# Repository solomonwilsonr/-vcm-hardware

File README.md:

<h1 align="center">VCM — Version Control for Hardware</h1>

<p align="center">
  Semantic diffs · Evidence-backed impact · Physical fleet traceability
</p>

<p align="center">
  <a href="#quickstart">Get started</a> ·
  <a href="#visual-tour">Visual tour</a> ·
  <a href="docs/architecture.md">Architecture</a> ·
  <a href="docs/hackathon.md">Hackathon</a> ·
  <a href="CONTRIBUTING.md">Contribute</a>
</p>

<p align="center"><strong>Python 3.11+ · Apache-2.0 · Working MVP · Offline core</strong></p>

**Every hardware change has a blast radius. VCM makes it traceable.**

VCM is an engineering-aware version-control and intelligence layer for **datacenter node and rack
hardware**. You commit a node's configuration the way you commit code; VCM tells you what a change
to it breaks, which physical units are affected, and how much to trust each thing it says.

It is built around three questions:

1. **What exactly changed in this configuration?** A semantic diff of the node inventory —
   accelerators, CPUs, memory, NICs, power supplies, slots and the domains they share — not changed
   bytes in a manifest.
2. **What else could that change affect, and what evidence supports it?** A dependency graph plus an
   offline impact report whose findings are labelled `verified`, `rule_based` or `speculative`, each
   with evidence links back to a file and hash.
3. **Which physical units were built from the affected configuration?** Releases pin artifact
   hashes; nodes are registered against releases and can be looked up by component or revision.

> Built for the Appwrite Databases Hackathon: see [docs/hackathon.md](docs/hackathon.md).

> **Status: working MVP, honest scope.** Everything marked *Implemented* below runs and is covered
> by tests in this repository. Everything marked *Planned* does not exist yet. See
> [Limitations](#limitations).

## Explore the documentation

- [Quickstart](#quickstart) — install, compare two revisions and open the dashboard.
- [Hardware workflows](#work-with-your-own-hardware) — inventory, signing, fleet, sync and agents.
- [Appwrite](#what-lives-in-appwrite-and-why) — shared fleet, semantic search and graph storage.
- [Feature status](#modules-implemented-vs-planned) · [Confidence classes](#confidence-classes) · [Limitations](#limitations).
- [Architecture](docs/architecture.md) · [Data model](docs/data-model.md) · [Roadmap](docs/roadmap.md) · [Demo script](docs/demo-script.md).

## The demo in one paragraph

A node runs eight A100 PCIe accelerators on four 2000 W supplies in a 2+2 redundant bank. Someone
proposes swapping them for H100 NVL. The manifest diff is eight replaced line items. What VCM says
is that the node now draws **4190 W against a 4000 W usable budget**, so losing one supply drops it;
that the **installed driver (470.223.02) is below the H100's minimum (525.60.13)**, so the cards
will not initialise at all, and that CUDA 11.4 is below their 12.0 minimum; that the chassis is
rated for 3600 W of cooling; that the Gen5 cards sit on a Gen4 host root; that both PCIe roots are
lane-oversubscribed; and that the power connector changed from 8-pin EPS to 12VHPWR, so the existing
harness does not fit.

None of that is written down anywhere. It falls out of the graph plus a component catalog.

```
$ vcm impact v1.0 v1.1
Findings: verified 6, rule_based 9, speculative 3 | severity: critical 3, warning 9, info 6
```

Then it checks the premise. Fed the machine's own Redfish and `nvidia-smi` output, `vcm drift`
reports that v1.0 was never quite true: a DIMM has failed and the driver actually installed is
older than the one declared. The fleet commands say which racks go over budget if every unit on the
old release is upgraded, and plan the rollout in waves of at most one unit per rack, holding back
every unit whose change still has critical findings.

## Visual tour

An 18-second, silent preview made from existing page captures with camera movement.
The comparison screen is the running dashboard; graph and fleet scenes are landing-page
illustrations. This is an edited tour, not a recording of live telemetry.

### Compare revisions and inspect the evidence

The dashboard brings the revision pair, changed components, impact severity, catalog trust and
confidence classes into one view. This captured demo includes attached machine observations;
its finding counts differ from the declaration-only CLI example above.

<details>
<summary><strong>See the landing page</strong></summary>

The landing page introduces the product. It is deployed at
<http://vcm-site-061664787595.s3-website-us-east-1.amazonaws.com> (S3 static hosting; HTTPS via
CloudFront is pending AWS account verification). Run it locally with
`python3 -m http.server 8080 --directory site`, then open <http://127.0.0.1:8080>.
The authenticated dashboard is served by `vcm serve` below.

</details>

See [media sources and regeneration instructions](docs/assets/README.md).

## Quickstart

### 1. Clone and install

Requires **Python 3.11+**. These commands use a macOS/Linux shell; the demo scripts also
require Bash, Make and `sha256sum` (GNU coreutils). The core has no third-party dependencies;
`.[dev]` installs the API, Appwrite SDK and development tools.

```bash
git clone https://github.com/solomonwilsonr/-vcm-hardware.git
cd -- -vcm-hardware
python3 -m venv .venv
source .venv/bin/activate
python -m pip install -e ".[dev]"
vcm --help
```

### 2. Create a sample hardware repository

Run these from the project root. Keep the sample fleet local even if you already have
Appwrite credentials configured. Choose an empty directory for `my-node`.

```bash
export VCM_FLEET_LOCAL=1
mkdir my-node
cp -R examples/gpu-node/v1.0/. my-node/
vcm init my-node
vcm -C my-node commit -m "Baseline: A100 node" --tag v1.0
cp -R examples/gpu-node/v1.1/. my-node/
vcm -C my-node commit -m "Proposed upgrade: H100 NVL" --tag v1.1
vcm -C my-node diff v1.0 v1.1
vcm -C my-node impact v1.0 v1.1
```

Expect eight accelerator replacements and findings about power, cooling, firmware and
connectors. Each finding carries its confidence class and evidence.

### 3. Open the dashboard

```bash
vcm -C my-node token create demo --role approver
vcm -C my-node serve --port 8000
```

Save the token printed by the first command; it is shown only once. Open
<http://127.0.0.1:8000/#/compare> and paste it into the browser's token prompt.
Select **v1.0** as the base and **v1.1** as the head, then click **Compare**.
Stop the server with `Ctrl+C`.

### 4. Run the complete demo and checks

From the project root, with the virtual environment active:

```bash
make test
make lint
make demo
```

`make demo` adds observed drift, releases, signed unit passports, racks, rollout planning,
reviews and audit verification. It **recreates `demo-workspace/` on each run** and ends by
intentionally corrupting a stored blob to prove that release verification detects tampering.
Use the clean `my-node` repository above for interactive exploration.

### 5. Optional: connect a shared Appwrite fleet

The local walkthrough needs no credentials. To connect a shared fleet, copy
[`.env.example`](.env.example) to `.env` if you do not already have one, fill in your
endpoint, project, API key and database ID, then run:

```bash
unset VCM_FLEET_LOCAL
vcm fleet health
vcm fleet provision
```

The required API-key scopes are documented in `.env.example`. Keep credentials in `.env`;
never commit them. See [the Appwrite guide below](#what-lives-in-appwrite-and-why) for
semantic part search and the optional shared graph. `make demo-fleet` demonstrates two
checkouts sharing the registry and **writes demo units to your configured Appwrite project**.

## Work with your own hardware

On your own node:

```bash
vcm init .
vcm commit -m "current config" --tag v1.0     # snapshot every file, categorised by type
# ...edit the node manifest...
vcm commit -m "proposed upgrade" --tag v1.1
vcm diff v1.0 v1.1                            # semantic diff
vcm impact v1.0 v1.1                          # impact report (--json for JSON)
vcm catalog coverage --rev v1.1               # what the catalog can actually reason about
vcm validate --rev v1.1 --compare v1.0
vcm release create R1 --rev v1.1              # pin hashes
vcm release verify R1
vcm device register NODE-0001 --release R1 --batch RACK-12
vcm device affected --component GPU0 --value "NVIDIA A100 PCIe 40GB"
vcm rollback plan v1.0 --from v1.1
vcm timeline ; vcm explain v1.0 v1.1
```

### Check the declaration against the machine

```bash
vcm inventory fetch-redfish https://10.0.0.21 --user ro --out bmc.json   # explicit network call
nvidia-smi --query-gpu=index,name,serial,pci.bus_id,driver_version,power.draw,power.limit,\
pcie.link.gen.max,pcie.link.width.max --format=csv > gpus.csv
vcm drift --rev v1.0 --redfish bmc.json --nvidia-smi gpus.csv --attach
vcm inventory manifest --redfish bmc.json --out draft.node.json        # bootstrap a manifest
```

Before trusting a new capture, ask it what it left out:

```bash
vcm inventory doctor --redfish bmc.json --nvidia-smi gpus.csv
```

The doctor lists Redfish resources that could not be fetched, kinds that were present but not read,
component types the capture cannot vouch for (drift will not judge them), and parts too thinly
described to match. A parser that is quiet about what it skipped makes a gap look like a clean
result; this is how you find out. To share a capture, or add it to the test suite, scrub it first:

```bash
vcm inventory sanitize --redfish bmc.json --nvidia-smi gpus.csv --out tests/captures/<vendor>-<model>
```

That replaces serials, hostnames, addresses, UUIDs and secrets with stable same-shape stand-ins
(identifiers correlate across files, model names, part numbers and firmware versions are left
alone, and the scrubbed capture parses exactly as the original did), seals the folder with
checksums, and drafts an `expect.json`. The folder then becomes a regression test automatically;
see [`tests/captures/README.md`](tests/captures/README.md). The scrubber cannot know what a site
considers sensitive in free text: read the output before you share it.

`vcm drift` compares only the component types a source can see: a capture without NICs is never
read as "NICs missing". With `--attach`, the observation becomes evidence on the revision, and the
next impact report says whether the base was true, sets measured draw beside the declared estimate,
and projects the new configuration's draw (labelled `speculative`).

### Sign, audit, authenticate

```bash
vcm key gen release-eng --trust               # private key in ~/.vcm/keys, public in trustdb.json
vcm release sign R1 --key release-eng
vcm release verify R1 --require-signature
vcm device sign NODE-0001 --key release-eng
vcm audit verify                              # every commit, release, signature, lock: hash-chained
vcm token create alice --role approver        # API tokens are stored hashed, shown once
vcm serve                                     # binds 127.0.0.1; refuses to start without a token
```

### Fleet

```bash
vcm fleet rack define RACK-12 --budget 17000
vcm fleet place NODE-0001 --rack RACK-12 --position 20      # or: vcm fleet netbox --devices devices.json
vcm fleet query --type gpu --firmware "gpu_driver<535"       # --csv for spreadsheets
vcm fleet recall --mpn M393A4K40DB3                           # grouped by rack and release
vcm fleet power --upgrade-to v1.1 --release R1                # exits 1 if a rack goes over budget
vcm fleet rollout --to v1.1 --release R1 --max-per-rack 1     # waves; blocks critical, defers over-budget
```

### Team sync and locks

```bash
vcm remote add origin /mnt/shared/vcm/gpu-node
vcm push ; vcm pull                            # fast-forward only: VCM never merges hardware
vcm lock acquire gpu-node-01.node.json --reason "re-pinning PSUs" --ttl 4
vcm lock release gpu-node-01.node.json
```

Divergent histories are reported with the way out (compare both sides, keep one, re-apply the
other), never merged. Tags and records that differ between clones are listed as conflicts and left
alone. Commits and pushes that touch a file someone else has locked are refused.

### Let an AI agent use VCM (MCP)

`vcm mcp` serves VCM over the Model Context Protocol on stdio. It runs offline, needs no API key,
and opens no sockets. Point any MCP client at it, for example in `.mcp.json`:

```json
{"mcpServers": {"vcm": {"command": "vcm", "args": ["-C", "/path/to/repo", "mcp"],
                        "env": {"VCM_AGENT_NAME": "claude"}}}}
```

The agent gets 23 read-only tools (diff, impact with confidence labels and evidence, drift against
inline captures, a capture doctor, catalog lookup and review priority, a claim checker, fleet query and recall, rack power, rollout plan, policy check,
release and audit verification, passports, rollback) and two prompts (`review_change`,
`fleet_upgrade_plan`). Its server instructions tell it to report each finding's confidence class and
never upgrade it.

It changes nothing itself. The single write tool, `vcm_propose`, records a **pending proposal** for
one of five actions (create a release, open a review, place a unit, define a rack, register a unit).
A person decides:

```bash
vcm proposal list --status pending
vcm proposal show P0001
vcm proposal approve P0001 --by dana     # performs it as dana, after re-checking it still holds
vcm proposal reject P0001 --by dana --reason "not this quarter"
```

An agent cannot approve, and the person must differ from the proposer. Signing, catalog reviews
(they record that a human checked a datasheet), policy overrides, commits, remotes and locks are
**not proposable**: they stay human. Proposals are validated when made and again when approved; a
release that policy would block cannot even be proposed. The audit log records the agent as
proposer and the person as approver. The API exposes the same decision, needing an `approver`
token.

### Keeping agents honest

An agent can misquote a report: cite a finding that does not exist, promote a `rule_based` finding
to `verified`, round 4190 W into 4000 W, or omit the one critical finding that mattered.
`vcm_check_claims` catches that mechanically before the answer goes out. The agent submits what it
is about to say (finding ids, the confidence class and severity it will state, the numbers it will
quote); VCM recomputes the report itself and returns every mismatch plus every critical finding
that went unmentioned. The `review_change` prompt tells the agent to call it and not to answer
until `honest` is true. It cannot catch bad *reasoning* about correct facts.

`vcm eval` grades an agent on five tricky cases: the headline upgrade, a part the catalog has never
heard of, a base that does not match the machine (and a projection that is only a prediction), a
change that touches nothing (do not invent problems), and instructions planted in a commit message
(data, not orders). Grading is mechanical: claims checked as above, no invented figures or finding
ids, never "safe", and case-specific honesty.

```bash
vcm eval run                         # the honest reference answerer: must pass 5/5
vcm eval run --agent sloppy          # flawed on purpose: must fail (CI checks both)
vcm eval run --agent "python my_agent.py"   # yours; see vcm_mcp.evals.external_agent
```

An external agent gets one JSON object on stdin (`question`, `repo`, `a`, `b`, `mcp_command`) and
prints `{"text": ..., "claims": [...]}`. **No live model has been run against these cases yet.**
Until one has, a pass means only that the grader and the reference agree.

### Policies and site rules

```json
{"schema": "vcm-policy/1", "rules": [
  {"id": "no-critical", "forbid_severity": "critical"},
  {"id": "known-parts", "forbid_unknown_parts": true},
  {"id": "power-needs-two", "require_approvals": 2, "when": {"title_matches": "power|supply"}},
  {"id": "signed", "require_signed_release": true, "stages": ["verify"]}]}
```

Commit this as `vcm-policy.json`. `vcm policy v1.0 v1.1` checks a change; `vcm release create`
refuses a violating release unless `--override-policy REASON` is given, and the override is written
into the manifest and the audit log. Site-specific rules are Python plugins (see
[`examples/plugins/site_rules.py`](examples/plugins/site_rules.py)), enabled with
`VCM_RULE_PLUGINS=module:function` or the `vcm.rules` entry-point group.

### Node manifests

A node is described by a `*.node.json` file. Components declare what they are and which domains
they share; everything else you put on a component is carried through and available to rules.

```json
{
  "schema": "vcm-node/1",
  "node": "gpu-node-01",
  "chassis": {"model": "Supermicro SYS-420GP-TNR", "cooling_w": 3600},
  "power": {"domains": {"PSU_BANK": {"redundancy": "2+2", "watts_each": 2000,
                                     "overhead_w": 400}}},
  "firmware": {"gpu_driver": "535.129.03", "cuda": "12.2"},
  "components": [
    {"ref": "GPU0", "type": "gpu", "model": "NVIDIA H100 NVL 94GB",
     "mpn": "900-21010-0000-000", "slot": "PCIE_SLOT1", "form_factor": "FHFL dual-slot",
     "tdp_w": 400, "pcie_gen": 5, "pcie_lanes": 16, "power_connector": "12VHPWR (16-pin)",
     "connections": {"power": "PSU_BANK", "pcie": "CPU0_PCIE_ROOT",
                     "interconnect": "NVLINK_FABRIC"}}
  ]
}
```

A power domain behaves exactly as a supply rail does on a board, which is why the same graph, diff
and impact engine serve both. Domains shared by every component (a PSU bank, or ground on a board)
are deliberately **not** followed when computing blast radius — otherwise every change would report
the whole node as affected.

## What lives in Appwrite, and why

VCM stores two very different kinds of thing, and they belong in different places.

**Derived data belongs on your disk.** The object store, snapshots and the dependency graph can all
be rebuilt from the design files in front of you. Nothing is lost by keeping them local, so the
graph's default backend is SQLite.

**Facts about physical hardware do not.** A unit is a machine that was built and shipped. It is
registered by whoever is standing in front of it and asked about later by someone else entirely —
an operator planning a rollout, a technician scanning the QR sticker on a front panel, an engineer
running a recall after a bad batch of accelerators. Those are different people on different
machines reasoning about the same hardware.

So the **unit and rack registry is the fleet of record, and it lives in Appwrite TablesDB.** The
local JSON files are a cache. This is not a swappable backend; it is the only arrangement in which
the registry is correct. With a per-clone registry, two engineers who clone the repository have two
different fleets, and this —

```bash
vcm device affected --component GPU0 --value "NVIDIA A100 PCIe 40GB"
```

— silently answers about whichever subset of the fleet that laptop happens to know about. A recall
query is the single question VCM must never get half-right.

```bash
cp .env.example .env     # endpoint, project, API key
vcm fleet health         # is the fleet of record reachable, and how big is it?
vcm fleet provision      # create the fleet tables, columns and indexes
vcm device register NODE-0001 --release R1
vcm fleet recall --model "A100"      # every unit, registered from any machine
```

Two behaviours differ on purpose, because the failure modes are not symmetric:

- **Writes fail closed.** If the fleet of record is unreachable, registering a unit raises and
  nothing is written locally either. A unit recorded only on the laptop that registered it is
  exactly the bug this fixes, so a loud failure beats a half-written registration.
- **Reads degrade open.** Reads fall back to the local mirror when the service is unreachable, but
  the store remembers that it did, and every command that reports to a human prints
  `fleet: LOCAL CACHE, possibly stale`. Stale answers are useful offline; silently stale ones are
  not.

One consequence is worth stating plainly: the registry is shared, but design history is not. A
clone can meet a unit built from a revision it has never fetched, and VCM reports that unit by
serial rather than dropping it or failing the query:

```
DEMO-B1   rack -   release R1   GPU0=NVIDIA A100 PCIe 40GB, ... (+4)
1 unit(s), 8 component(s); by rack: (unplaced) 1
  UNRESOLVED DEMO-A1: revision 9d9e3545fd is not in this checkout (fetch it before closing the incident)
fleet: shared (Appwrite TablesDB)
```

An incident cannot be closed on a silently partial fleet, which is the whole reason the registry
moved out of the checkout.

Without credentials, everything above keeps the old on-disk behaviour with no flags, which is how
the test suite runs. `VCM_FLEET_LOCAL=1` forces it. Repository-scoped records — releases, pull
requests, agent proposals — stay in the checkout, because they travel with the files they describe.

### Semantic part search on VectorsDB

The catalog matches by part-number prefix, which answers *what is this part* and nothing else. When
a part goes end of life the question is the other one — *what could I put here instead* — and
"a dual-slot 300 W accelerator I can run on an existing 8-pin harness" names no part at all.

So the catalog is embedded into **Appwrite VectorsDB** and searched by meaning:

```bash
vcm catalog provision                       # vector collection, dimension probed from the model
vcm catalog index                           # embed all 90 parts
vcm catalog similar "dual-slot 300 W accelerator on an 8-pin harness"
vcm catalog replace "NVIDIA A100 PCIe 40GB"
```

A nearest-neighbour hit is a *plausible* candidate, and plausible is not the standard the rest of
VCM reports at. So `replace` runs every candidate back through the deterministic catalog facts —
type, socket, connector, slot width, PCIe generation, driver floor — and labels it:

```
Replacements for NVIDIA A100 PCIe 40GB (gpu):
  CHECK         NVIDIA H100 NVL  (unreviewed)
                needs a 12VHPWR connector, installed part uses 8-pin EPS
                draws 400 W against 250 W
                requires driver 525.60.13 (installed part needs only 450.80.02)
  INCOMPATIBLE  NVIDIA H100 SXM5  (unreviewed)
                different socket (PCIe vs SXM5)
```

Semantic search proposes; the rule data disposes. The same discipline as the rest of the engine:
nothing is reported as more certain than it is.

### The shared dependency graph

The graph has an Appwrite backend too, for teams that want impact analysis queryable fleet-wide
rather than rebuilt per machine. Unlike the registry this one is genuinely optional — the data is
derived, so SQLite loses nothing but shareability.

```bash
vcm graph provision
vcm graph push --rev v1.1
vcm graph query --component GPU0 --rev v1.1 --backend appwrite
```

Row ids are deterministic hashes, so a re-push upserts rather than duplicating; writes are batched
into bulk upserts; and a revision's subgraph is paged into memory once for traversal, or queried
live with `prefetch=False`. The test suite asserts that an Appwrite-backed graph returns
**byte-identical** results to the local SQLite one.

> **What has actually been run.** Every Appwrite path is exercised against a faithful in-process
> fake (`tests/fake_appwrite.py`) under both SDK response shapes, because the suite must pass
> without network. Beyond that: the **fleet store has been run against a live Appwrite project** —
> provisioned, and verified with two separate clones registering units into one fleet, including
> the cross-clone duplicate rejection and the stale-cache path. The **VectorsDB path has not been
> run live**: it needs the `embeddings.write` and `vectors.*` scopes on the API key, and the
> commands say so when they are missing.

## Modules: implemented vs planned

| # | Module | Location | Status |
|---|--------|----------|--------|
| 1 | Content-addressed object store, snapshots, branches, tags, commit/log/checkout/diff, evidence store | `packages/core` | **Implemented** |
| 2 | Hash-chained audit log of every state change | `packages/core` (`vcm_core.audit`) | **Implemented** |
| 3 | Ed25519 signing of releases and unit passports, trust database | `packages/core` (`vcm_core.signing`) | **Implemented** in pure Python (RFC 8032 vectors tested) |
| 4 | Remotes (shared directory), push/fetch/pull, file locks | `packages/core` (`vcm_core.remote`) | **Implemented**, fast-forward only by design. No S3 or Git transport |
| 5 | Input parsers: node manifests (`*.node.json`), KiCad `.kicad_sch`/`.kicad_pcb`, BOM CSV | `packages/file-parsers` | **Implemented**. Node manifests are the primary format; the board parsers are retained from VCM's origin and still work |
| 6 | Observed inventory: Redfish captures, `nvidia-smi` CSV/XML, manifest drafting | `packages/file-parsers` (`vcm_parsers.inventory`) | **Implemented** against saved captures and a synthetic sample. Live Redfish capture exists but has **not been run against a real BMC** here |
| 7 | Semantic diff engine, and drift (manifest vs machine) | `packages/diff-engine` | **Implemented** |
| 8 | Engineering dependency graph | `services/engineering-graph` | **Implemented**, with two interchangeable backends: local SQLite and **Appwrite TablesDB** for a shared fleet-wide store |
| 9 | Impact analysis | `services/ai-engine` | **Implemented** as a deterministic rule engine over a component catalog. Node rules: power budget under redundancy policy, chassis cooling, PCIe generation and lanes, driver/CUDA/BIOS/BMC minimums, power connector, DDR generation, DIMM mixing and channel population, socket fit and mixed CPUs, mixed accelerators on one fabric, NIC vs fabric speed, slot count, and measured draw from attached observations. LLM provider interface exists with a no-op default; no real LLM provider ships |
| 10 | Rule plugins for site-specific checks | `services/ai-engine` (`vcm_ai.plugins`) | **Implemented**. Plugins cannot emit `verified` findings; a crashing plugin becomes a finding |
| 11 | Component catalog | `services/ai-engine` | **Implemented**: 90 parts across layers, user and project overrides, JSON/CSV import, per-field source attribution, review worksheets ranked by what your units use, and a trust figure on every report. **No bundled part is reviewed** |
| 11b | Semantic part search | `services/ai-engine` (`vcm_ai.semantic`) | **Implemented** on **Appwrite VectorsDB**: the catalog is embedded and searched by meaning, then every candidate is checked against catalog facts and labelled `drop_in`/`check`/`incompatible`. Tested offline against a fake embedding and vector service; **not run against a live VectorsDB** |
| 12 | Validation | `services/validation` | **Implemented**: built-in checks plus an optional `kicad-cli` wrapper for the board domain (skipped when absent) |
| 13 | Release manifests, verification, rollback planner | `packages/workflow` | **Implemented** (JSON/YAML manifest, re-hash verification, signatures, policy record) |
| 14 | Policies as code (`vcm-policy.json`) gating checks, reviews, releases and verification | `packages/workflow` (`vcm_workflow.policy`) | **Implemented** |
| 15 | Physical traceability: unit registry, signed passports, QR | `services/traceability` | **Implemented**. The unit registry is **Appwrite TablesDB** when configured, so one fleet is shared by every machine; local JSON is the offline cache. Pure-Python QR encoder |
| 16 | Fleet: racks, placement, queries, recalls, rack power, rollout waves, NetBox import | `services/traceability` (`vcm_trace.fleet`, `vcm_trace.fleet_store`, `vcm_trace.netbox`) | **Implemented**. Racks and placement share the fleet store; writes fail closed, reads fall back to the cache and say so. NetBox import tested against saved API JSON, **not against a live NetBox** |
| 17 | Change review records | `packages/workflow` | **Partial**: diff, impact, validation, comments, approvals, policy-aware readiness, identity via API tokens. No merge action |
| 18 | Time machine (`timeline`, `explain`) | `packages/workflow` | **Implemented** |
| 19 | CLI, REST API, dashboard | `packages/vcm-cli`, `services/api` | **Implemented**. The API requires a token (roles: viewer, editor, approver, admin) and refuses to start without one unless `--insecure`. The dashboard's **Setup** page draws every part of a node, the domains they share, the attached machine capture, and the units and racks, and re-reads the repository every 5 s ("live" means polling the repository, **not** telemetry from machines: machine data appears only where a capture was attached with `vcm drift --attach`) |
| 20 | Agent access: MCP server (stdio, offline) with read-only tools and a propose-then-human-approves write path | `services/mcp-server` (`vcm_mcp`) | **Implemented**. Tested over a real stdio subprocess; **not yet exercised with a live agent client**. The dashboard's **Agents** page lists proposals and lets a signed-in approver approve or reject them (the API refuses agents, the proposer and unauthenticated callers) |
| 21 | Agent honesty: claim checker (`vcm_check_claims`) and evals (`vcm eval`) | `vcm_ai.claims`, `vcm_mcp.evals` | **Implemented**. Evals have been run only against reference answerers (one honest, five deliberately flawed), **never against a live model** |
| 22 | Integrations and apps: KiCad plugin, FreeCAD, Git bridge, web app, desktop app | `integrations/`, `apps/` | **Planned**: README stubs only |

## Confidence classes

Every finding has exactly one `confidence_class`, plus evidence links (`file` with hash, `ref`,
`commit`, `db` with per-field attribution, `declared`, `evidence`, `plugin`). The report's shape is
published as [`docs/schemas/impact-report.schema.json`](docs/schemas/impact-report.schema.json)
(`vcm-impact/1`):

- `verified` — derived from parsed configuration data, declared project links or stored evidence.
- `rule_based` — a heuristic from engineering rules and the component catalog.
- `speculative` — a prediction; not established by data.

An optional LLM provider can only ever add `speculative` findings, and a site rule plugin only
`rule_based` or `speculative` ones; neither can state a fact. The default provider is a no-op
and VCM never calls the network by default.

**Silence is never safety.** If a changed component is not in the catalog, VCM says so explicitly
rather than returning a clean-looking report:

> **8 components: NVIDIA B200 SXM 192GB is not in the component catalog** — Affected: GPU0 … GPU7
> (part 900-74000-0000-000). The catalog has no entry, so VCM skipped driver-minimum, PCIe
> generation and power-connector checks, all of which read the catalog. Rules fed by values
> declared in the node manifest (power budget, chassis cooling, PCIe lane counts) did still run for
> it. Absence of warnings from those checks is absence of knowledge, not evidence of a safe change.

Note what that message does *not* do: it does not claim more ignorance than there is. Rules driven
by manifest-declared values keep working on an unknown part, and the disclosure says so rather than
flatly announcing that nothing ran.

Every impact report also carries a coverage summary (`Catalog covered 8 of 8 changed components`),
so a reader can always tell how much of the configuration the rules actually reasoned about.

## The component catalog

90 parts in three bundled layers, overridable per user (`~/.vcm/catalog/`) and per project
(`vcm-catalog/`, committed next to the configuration). Later layers win; lookup is longest-prefix,
so a specific part number beats a family entry.

```bash
vcm catalog list --type gpu
vcm catalog show "NVIDIA H100 NVL 94GB"
vcm catalog import our-parts.csv --scope project
```

**No bundled entry has been datasheet-reviewed.** Every part carries `reviewed: false` and a named
`source`; thermal resistance figures are package-typical estimates, not part data; TDP is a board
power rating, not measured draw under your workload.

Rule findings cite each value they used, field by field: whether it came from the node manifest or
the catalog, the catalog's source for that field, and who verified it. Record a review with

```bash
vcm catalog review 900-21010-0000-000 --by alice --source "H100 NVL datasheet DS-11717 p.3" \
    --confirm tdp_w --confirm min_driver --set pcie_gen=5
vcm catalog unreviewed --type gpu
```

A part becomes `reviewed: true` only once every rule-relevant field it carries has been verified by
a named person against a cited source.

To spend reviewing time where it buys the most trust:

```bash
vcm catalog priority                       # parts your registered units use most, and how much of
                                           #   each has been checked (0 of 31 values, today)
vcm catalog worksheet --top 15 --out review.csv
# a person opens review.csv: for each value they check against the datasheet, set decision to ok
# (or correct, with corrected_value), cite the document and page in datasheet_source, and put
# their own name in checked_by. Rows left blank are not touched.
vcm catalog review --from-csv review.csv   # every row is validated first; one bad row, nothing applied
```

The importer refuses a row with no named person, one naming an agent, one with no source, a
`correct` with no value, and an `ok` for a value that changed since the sheet was written (that
would verify a number nobody looked at). Every impact report then carries a trust figure
(`summary.trust`): how many catalog values its findings cite as evidence and how many a named person
verified. It is a floor, not a census: a rule may use inputs it does not cite individually.

## Limitations

- **The catalog is small and unreviewed.** 90 parts, none datasheet-verified by a human. Rules are
  heuristics and can be wrong or incomplete. VCM discloses what it does not know; it cannot
  disclose what it has wrong.
- Observed-inventory parsing is tested against a **synthetic** Redfish capture, and against
  **real** `nvidia-smi` output from an NVIDIA GB10 (DGX Spark), which is pinned as a fixture in
  `tests/test_real_hardware_gaps.py`. That first contact with real hardware found three bugs the
  synthetic fixtures could not: the scrubber treated the `[N/A]` a real card reports as an
  identity, `inventory doctor` called a capture complete when the machine had answered neither
  serial nor power limit, and a firmware-only change produced no diff at all. No sealed folder has
  been contributed to `tests/captures/` yet. BMC implementations vary; the live Redfish fetcher and
  the NetBox fetcher have not been run against real services here.
- Power and thermal rules use declared and catalog figures. Attached telemetry is a point-in-time
  reading under whatever workload was running, and projecting it onto a new configuration is a
  prediction, labelled as such.
- The board domain's schematic connectivity is not traced; nets come from PCB pad assignments. The
  sample KiCad files are hand-generated and have not been opened in KiCad.
- Remotes are a shared directory: no network transport, no server-side access control beyond the
  file system's. History is fast-forward only, by design; there is no merge.
- The shared fleet makes the **registry** fleet-wide, not the design history. A clone that has not
  fetched a unit's revision cannot describe that unit, and says so (`UNRESOLVED`) rather than
  omitting it. Pair it with `vcm remote` so engineers share history too.
- Row-level Appwrite permissions are **not** used yet: VCM talks to TablesDB with a server API key,
  which bypasses them. Access control is at the VCM API's token roles, so anyone holding the
  Appwrite key has full access to the fleet tables. Protect the key accordingly.
- Semantic part search depends on Appwrite's embedding models, and its shortlist is only as good as
  the catalog text behind it. Every candidate is checked against catalog facts before it is shown,
  but an unreviewed catalog entry can make a confident-looking verdict wrong.
- Signatures prove which trusted key vouched for a release or passport. The trust database is a
  committed file, so whoever can change and commit it decides whom to trust; protect it like code.
  The Ed25519 implementation is pure Python and **not constant-time**: fine for signing manifests
  offline, not for use where an attacker can time it.
- The audit chain detects edits and deletions, but someone with write access to `.vcm/` can rewrite
  the whole chain; signed releases anchor its head, which is what makes a rewrite detectable.
- API identities come from tokens; there is no SSO, password login or per-object permission. Use
  HTTPS in front of it if it leaves localhost.
- Evals and the claim checker grade honesty and fidelity to the report, not insight, and the evals
  have only been exercised with scripted answerers. A model that passes can still reason badly
  about correct facts; one that fails shows where to look.
- The MCP server is tested against the protocol (including a real stdio subprocess) but has not
  been driven by a live agent client here. An agent's reasoning is only as good as VCM's data: it
  inherits every limitation above, and an agent can still misread a result, which is why each
  finding carries its confidence class and evidence. Proposals are approved from the CLI, the API or the dashboard's
  Agents page; the dashboard needs an API token with the approver role to decide (insecure mode
  cannot).
- Integrations (KiCad, FreeCAD, Git bridge), the web app and the desktop app are not implemented.

## Repository map

```
packages/core            object store, snapshots, audit log, signing, remotes, tokens  (vcm_core)
packages/file-parsers    node manifests, observed inventory, KiCad, BOM               (vcm_parsers)
packages/diff-engine     semantic hardware diff, drift                                (vcm_diff)
packages/workflow        releases, rollback, reviews, policies, timeline              (vcm_workflow)
packages/vcm-cli         `vcm` command                                                (vcm_cli)
services/engineering-graph  dependency graph: SQLite + Appwrite                       (vcm_graph)
services/ai-engine       impact rules, rule plugins, component catalog                (vcm_ai)
services/validation      checks and evidence                                          (vcm_validation)
services/traceability    units, passports, QR, fleet, NetBox                          (vcm_trace)
services/api             FastAPI app + dashboard                                      (vcm_api)
services/mcp-server      MCP server for agents, proposals                             (vcm_mcp)
examples/gpu-node        sample node, v1.0 and v1.1, plus synthetic machine captures
examples/plugins         example site rules
examples/demo.sh         end-to-end node demo
examples/demo-pcb.sh     end-to-end board demo (the original domain)
docs/                    architecture, data model, roadmap, report schema
```

Licensed under Apache-2.0. See [CONTRIBUTING.md](CONTRIBUTING.md).

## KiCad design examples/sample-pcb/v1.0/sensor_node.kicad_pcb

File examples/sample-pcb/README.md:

# Sample project: sensor_node

A small ESP32-C3 based sensor node used by the VCM demo. Two revisions are provided:

| Revision | Change |
| --- | --- |
| `v1.0/` | 5 V in, AMS1117-3.3 LDO (SOT-223, 1 A) with 22 uF tantalum output capacitor |
| `v1.1/` | U1 swapped to MCP1700-3302E/TT (SOT-23, 250 mA), C2 changed to 10 uF ceramic, R1 nudged 1 mm |

Notes on the files:

- `*.kicad_sch` and `*.kicad_pcb` are hand-authored KiCad 8 S-expression files (generated programmatically,
  not exported from KiCad, and not opened in KiCad by the authors of this sample). The board is placement-only:
  no tracks or zones. The schematic ties pins to nets with global labels at the pin ends.
- The ESP32-C3 module footprint has an abbreviated pad list (8 of the real pads).
- `bom/*.csv` is the bill of materials, `vcm.json` declares firmware links, tests and rails for the dependency graph,
  `firmware/` is a stub, `tests/` holds test procedure notes.
- Component data used by the impact engine is in `services/ai-engine/vcm_ai/data/components.json`;
  it is a small illustrative subset and not a substitute for datasheets.

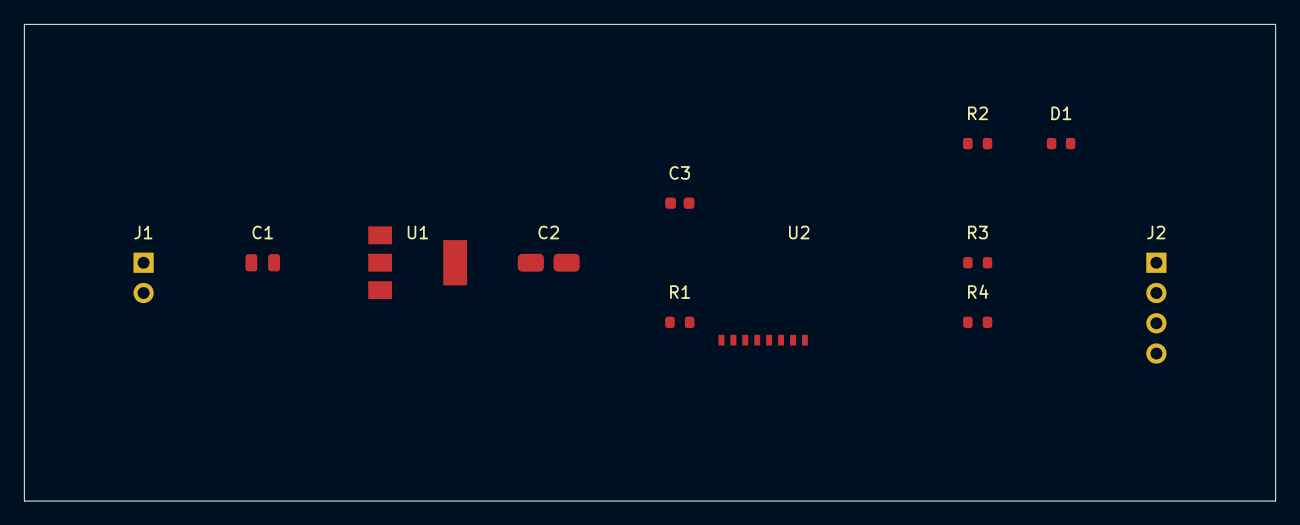
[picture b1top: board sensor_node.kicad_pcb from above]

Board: 2 copper layers, 105.0 x 40.0 mm, 12 parts (0 on the bottom side), 8 nets, no tracks yet.

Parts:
C1: 10uF; C_0805_2012Metric
C2: 22uF; CP_EIA-3528-21_Kemet-B
C3: 100nF; C_0603_1608Metric
D1: GREEN; LED_0603_1608Metric
J1: PWR_IN; PinHeader_1x02_P2.54mm_Vertical
J2: SENSOR; PinHeader_1x04_P2.54mm_Vertical
R1: 10k; R_0603_1608Metric
R2: 330; R_0603_1608Metric
R3, R4: 4.7k; R_0603_1608Metric
U1: AMS1117-3.3; SOT-223-3_TabPin2
U2: ESP32-C3-MINI-1

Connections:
+3V3: C2.1, C3.1, J2.1, R1.1, R3.1, R4.1, U1.2, U2.3
+5V: C1.1, J1.1, U1.3
EN: R1.2, U2.4
GND: C1.2, C2.2, C3.2, D1.1, J1.2, J2.2, U1.1, U2.1, U2.2, U2.13
LED_A: D1.2, R2.2
LED_DRV: R2.1, U2.10
SCL: J2.4, R4.2, U2.12
SDA: J2.3, R3.2, U2.11
